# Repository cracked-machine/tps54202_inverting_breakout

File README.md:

[HTML Version](https://cracked-machine.github.io/tps54202_inverting_breakout/)

# TPS54202 Inverting SMPS module

Breakout board for inverting buck boost SMPS using Texas Instrument's TPS54202

Based on example from this [app note](https://www.ti.com/lit/an/slva933/slva933.pdf)

|Paramater|Value|
|-|-|
|Input Voltage Range|12V nomimal, 8-16V|
|Output Voltage Range|-12V|
|Transient response, 50% load step|delta vout = 2.5%|
|Output Voltage Ripple|1%|
|Output Current Rating|Max 0.8 A|

Schematic can be found [here](docs/schematic/tps54202_inverting_breakout.pdf)

Layout can be found [here](docs/bom/ibom.html)

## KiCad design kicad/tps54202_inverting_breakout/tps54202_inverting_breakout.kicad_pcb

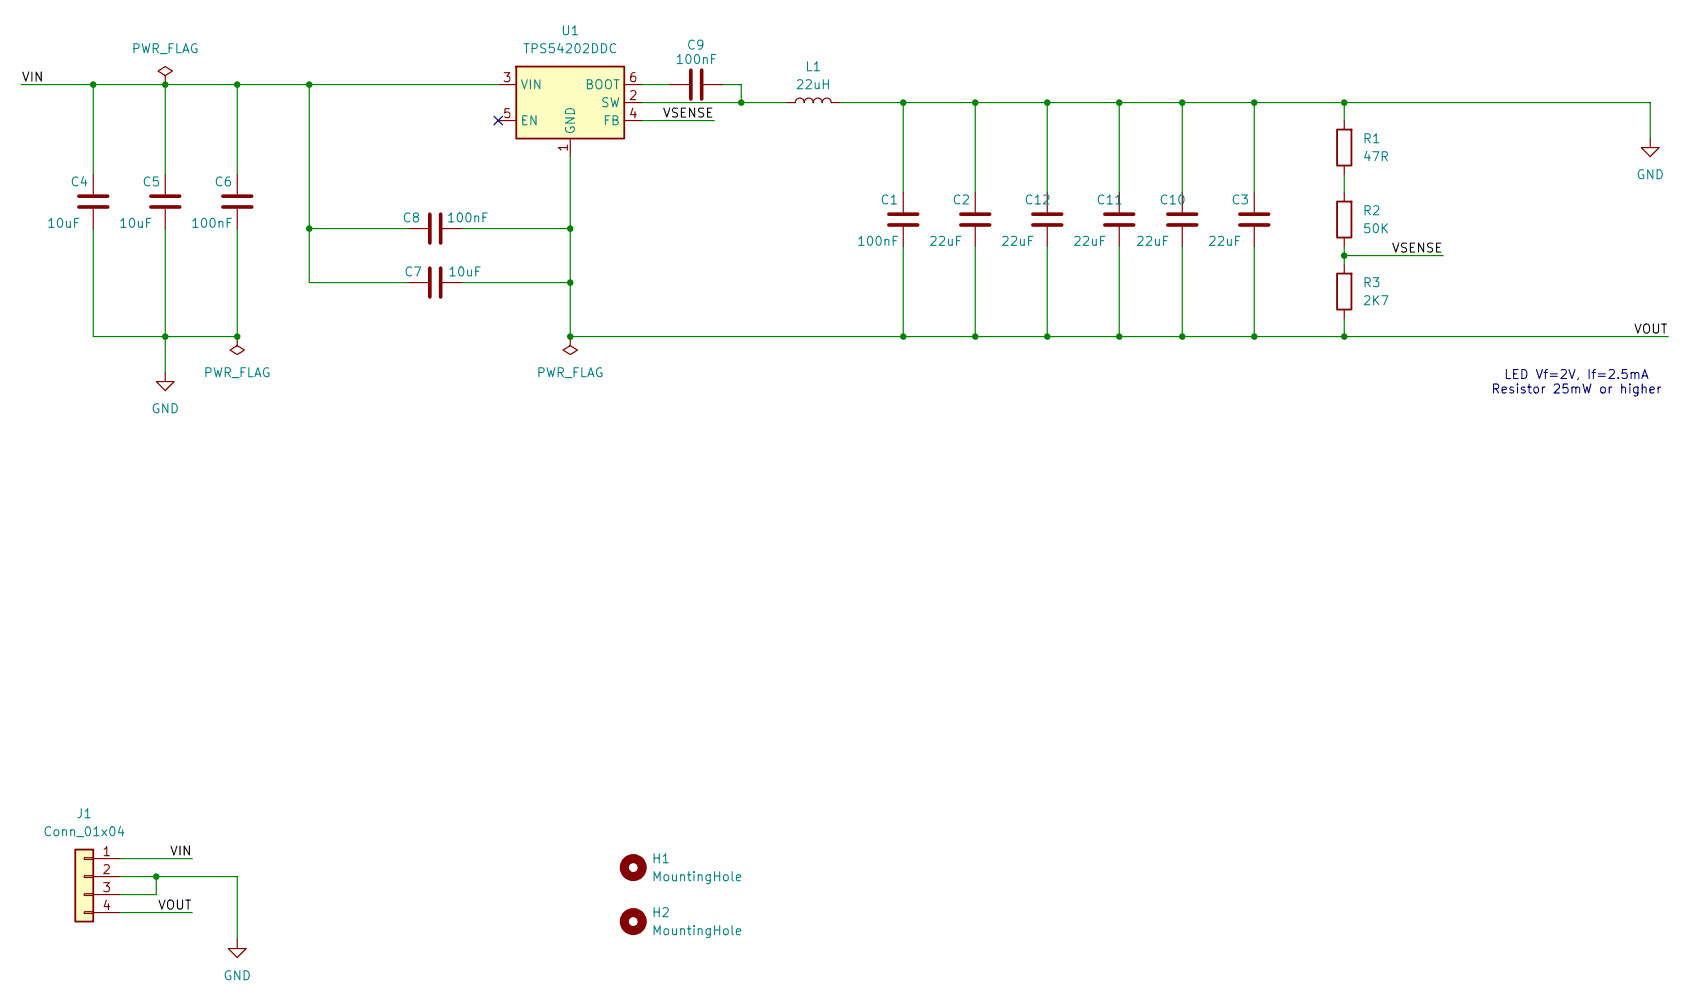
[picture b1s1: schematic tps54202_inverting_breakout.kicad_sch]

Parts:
C1, C6, C8, C9: 100nF; C_0805_2012Metric_Pad1.18x1.45mm_HandSolder
C2, C3, C10, C11, C12: 22uF; C_0805_2012Metric_Pad1.18x1.45mm_HandSolder
C4, C5, C7: 10uF; C_0805_2012Metric_Pad1.18x1.45mm_HandSolder
H1, H2: MountingHole; MountingHole_3.2mm_M3
J1: Conn_01x04; PinHeader_1x04_P2.54mm_Vertical
L1: 22uH; L_Bourns-SRN8040_8x8.15mm
R1: 47R; R_0805_2012Metric_Pad1.20x1.40mm_HandSolder
R2: 50K; R_0805_2012Metric_Pad1.20x1.40mm_HandSolder
R3: 2K7; R_0805_2012Metric_Pad1.20x1.40mm_HandSolder
U1: TPS54202DDC; SOT-23-6

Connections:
/VIN: C4.1, C5.1, C6.1, C7.1, C8.1, J1.1, U1.3 (VIN)
/VOUT: C1.2, C2.2, C3.2, C7.2, C8.2, C10.2, C11.2, C12.2, J1.4, R3.1, U1.1 (GND)
/VSENSE: R2.1, R3.2, U1.4 (FB)
GND: C1.1, C2.1, C3.1, C4.2, C5.2, C6.2, C10.1, C11.1, C12.1, J1.2, J1.3, L1.2, R1.2
unnamed: R1.1, R2.2
unnamed: C9.1, U1.6 (BOOT)
unnamed: C9.2, L1.1, U1.2 (SW)

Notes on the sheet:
LED Vf=2V, If=2.5mA Resistor 25mW or higher

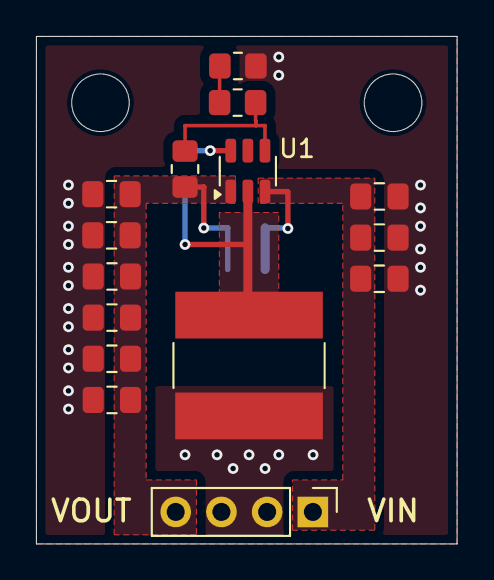
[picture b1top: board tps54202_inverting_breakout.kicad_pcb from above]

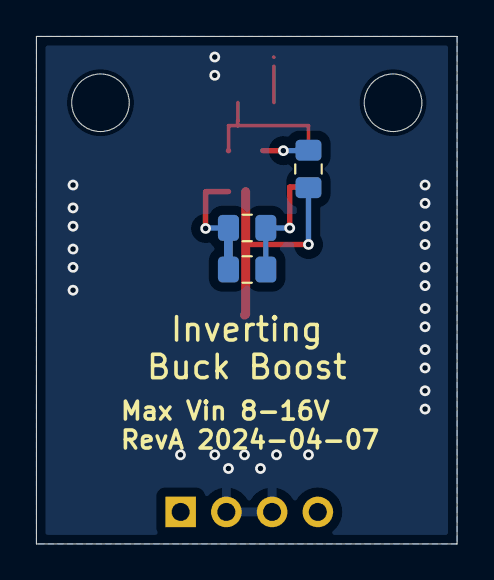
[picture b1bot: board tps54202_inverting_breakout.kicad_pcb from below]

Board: 2 copper layers, 23.4 x 28.2 mm, 20 parts (3 on the bottom side), 7 nets.

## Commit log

2024-04-07 RevA
2024-04-07 saved project
2024-04-28 RevB layout, added outut caps, tighter bypass coupling, improved layout
